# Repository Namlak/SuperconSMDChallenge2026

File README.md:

# SuperconSMDChallenge2026

The Hackaday Supercon X SMD Challenge board is here and it's an SAO for your badge!

Featuring parts from 1206 down to the insane 01005!

Since the SAO version of the board can't be worked on with the connector attached, a 3D-printable work stand STL file is included.

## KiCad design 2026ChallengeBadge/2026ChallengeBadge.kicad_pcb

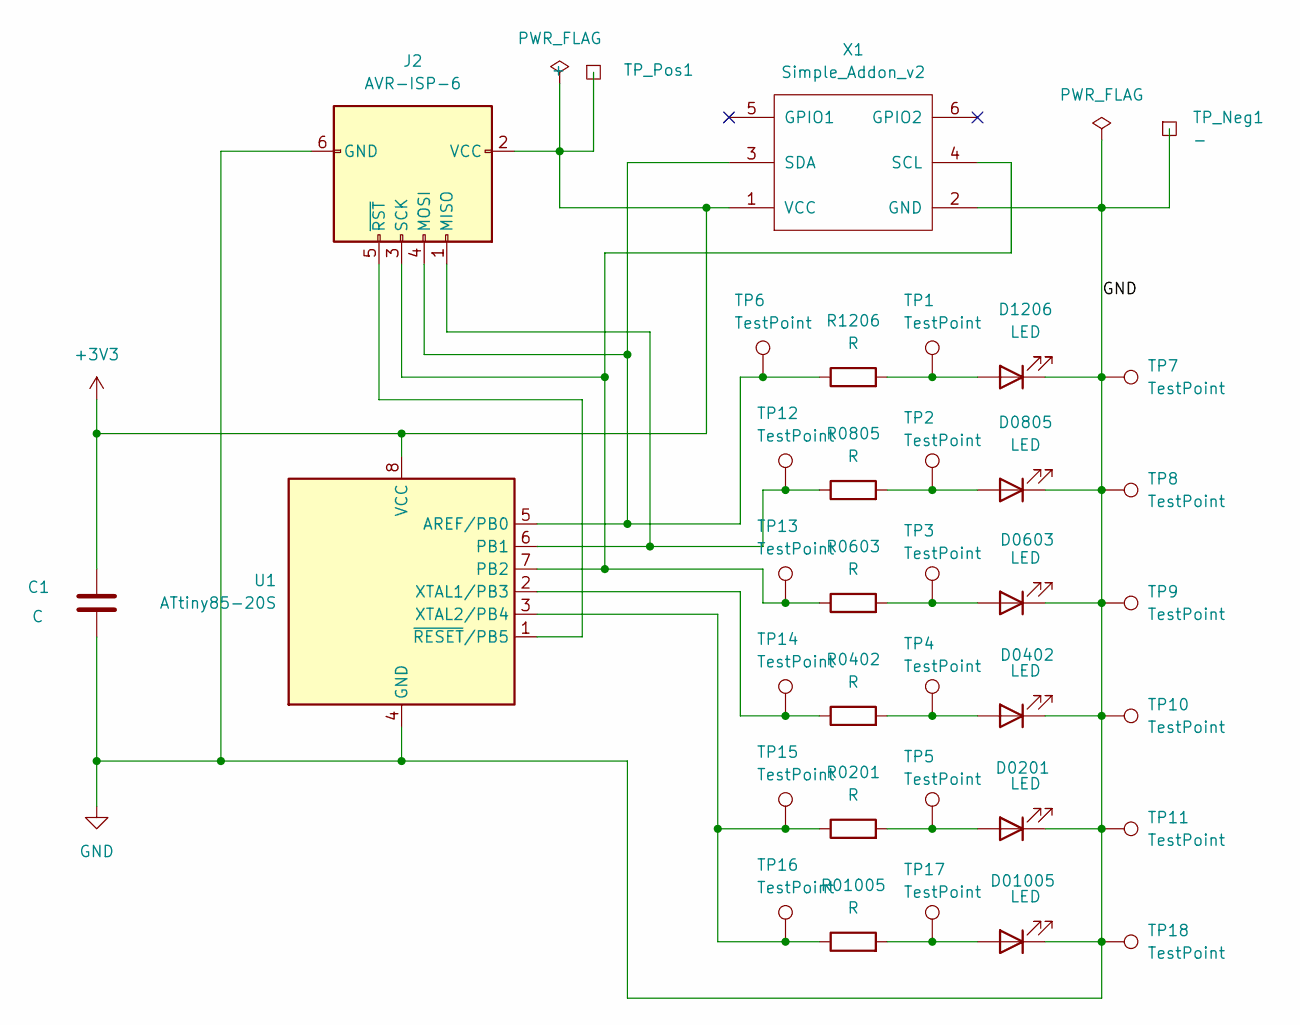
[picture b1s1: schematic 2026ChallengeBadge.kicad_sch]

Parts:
C1: C; C_1206_3216Metric_Pad1.33x1.80mm_HandSolder
D0201: LED; LED_0201_0603Metric_Pad0.64x0.40mm_HandSolder
D0402: LED; LED_0402_1005Metric_Pad0.77x0.64mm_HandSolder
D0603: LED; LED_0603_1608Metric_Pad1.05x0.95mm_HandSolder
D0805: LED; LED_0805_2012Metric_Pad1.15x1.40mm_HandSolder
D01005: LED; C_01005_0402Metric_Pad0.57x0.30mm_HandSolder
D1206: LED; LED_1206_3216Metric_Pad1.42x1.75mm_HandSolder
J2: AVR-ISP-6; Untitled
R0201: R; R_0201_0603Metric_Pad0.64x0.40mm_HandSolder
R0402: R; R_0402_1005Metric_Pad0.72x0.64mm_HandSolder
R0603: R; R_0603_1608Metric_Pad0.98x0.95mm_HandSolder
R0805: R; R_0805_2012Metric_Pad1.20x1.40mm_HandSolder
R01005: R; R_01005_0402Metric_Pad0.57x0.30mm_HandSolder
R1206: R; R_1206_3216Metric_Pad1.30x1.75mm_HandSolder
TP1, TP2, TP3, TP4, TP5, TP6, TP7, TP8, TP9, TP10, TP11, TP12, TP13, TP14, TP15, TP16, TP17, TP18: TestPoint; TestPoint_Pad_D1.0mm
TP_Neg1: -; TestPoint_Pad_2.0x2.0mm
TP_Pos1: +; TestPoint_Pad_2.0x2.0mm
U1: ATtiny85-20S; SOIC-8_5.3x5.3mm_P1.27mm
X1: Simple_Addon_v2; Simple_Addon_v2-SAO-2x3

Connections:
+3V3: C1.1, J2.2 (VCC), TP_Pos1.1 (1_1), U1.8 (VCC), X1.1 (VCC)
GND: C1.2, D0201.1 (K), D0402.1 (K), D0603.1 (K), D0805.1 (K), D01005.1 (K), D1206.1 (K), J2.6 (GND), TP7.1 (1_1), TP8.1 (1_1), TP9.1 (1_1), TP10.1 (1_1), TP11.1 (1_1), TP18.1 (1_1), TP_Neg1.1 (1_1), U1.4 (GND), X1.2 (GND)
unnamed: D0201.2 (A), R0201.2, TP5.1 (1_1)
unnamed: D0402.2 (A), R0402.2, TP4.1 (1_1)
unnamed: D0603.2 (A), R0603.2, TP3.1 (1_1)
unnamed: D0805.2 (A), R0805.2, TP2.1 (1_1)
unnamed: D01005.2 (A), R01005.2, TP17.1 (1_1)
unnamed: D1206.2 (A), R1206.2, TP1.1 (1_1)
unnamed: J2.1 (MISO), R0805.1, TP12.1 (1_1), U1.6 (PB1)
unnamed: J2.4 (MOSI), R1206.1, TP6.1 (1_1), U1.5 (AREF/PB0), X1.3 (SDA)
unnamed: J2.3 (SCK), R0603.1, TP13.1 (1_1), U1.7 (PB2), X1.4 (SCL)
unnamed: J2.5 (~RST), U1.1 (~RESET/PB5)
unnamed: R0402.1, TP14.1 (1_1), U1.2 (XTAL1/PB3)
unnamed: R0201.1, R01005.1, TP15.1 (1_1), TP16.1 (1_1), U1.3 (XTAL2/PB4)

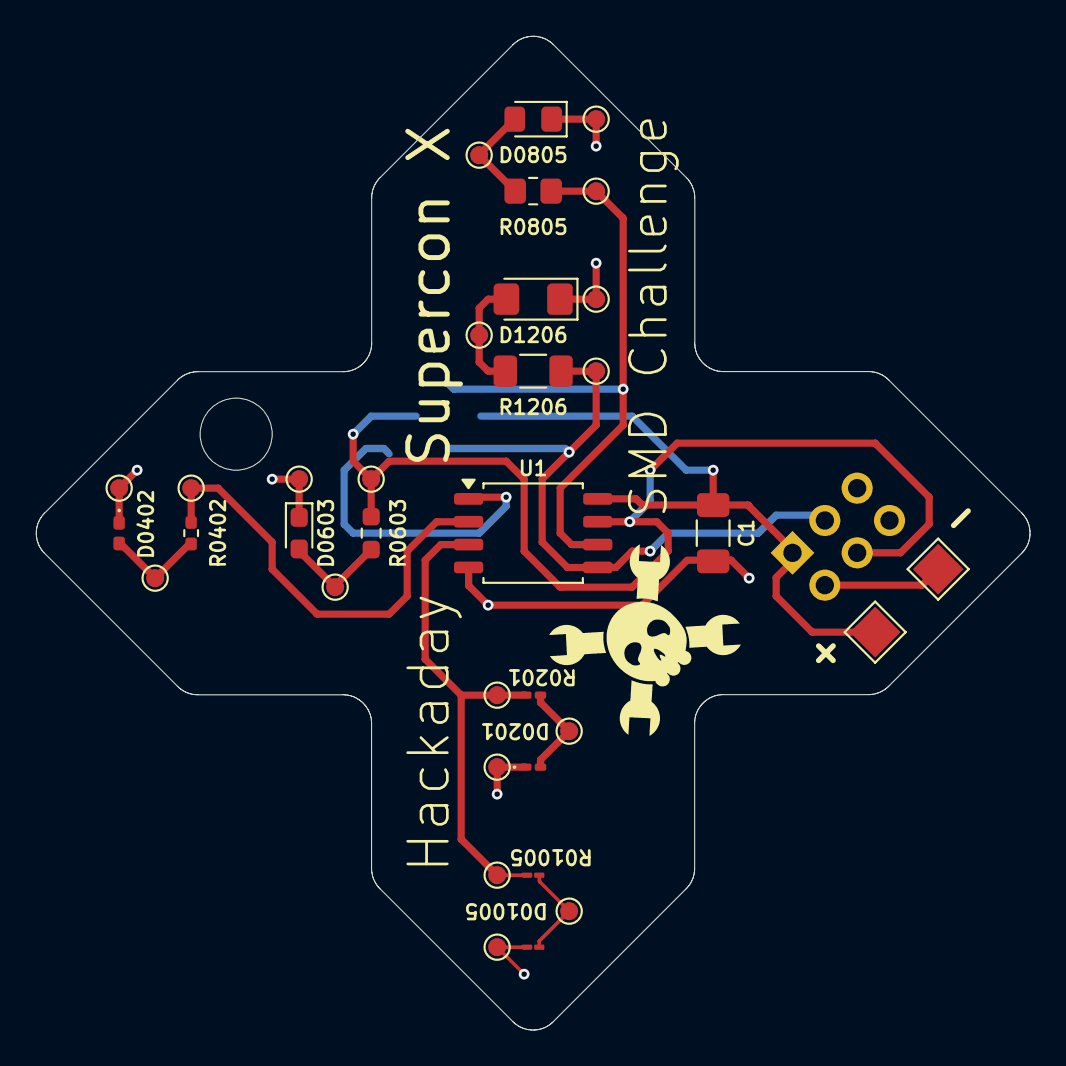
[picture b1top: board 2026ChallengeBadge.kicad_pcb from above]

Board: 2 copper layers, 55.2 x 55.2 mm, 36 parts (1 on the bottom side), 14 nets.
